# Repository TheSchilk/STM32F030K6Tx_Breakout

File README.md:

# STM32F030K6Tx Breakout

A very simple breakout board for the STM32F030K6Tx MCU. 

Philipp Schilk 2020

https://github.com/TheSchilk/STM32F030K6Tx_Breakout

## Overview

Besides SWD, 2 LEDs, space for a crystal and other supporting circuitry,
there are bells and whistles.

I did however aim to expose as much functionality of the STM as possible:
The crystal is optional and the IO can be exposed with two jumpers if needed.
Also the VDDA Supply can be separated from VDD if a separate supply is wanted.

In fact, with the right jumper configuration this board can serve as a direct
LQFP32 breakout board with all pins exposed and not set connections.

Because I hate nothing more than digging through PDFs to find out what
pins the LEDs where connected to again, I included as much information
as possible in the silkscreen. 

## Features on Board:

**ARM SWD**:  
Connector footprint can accept both an SMD and a TH programming header. 

See [TheSchilk/KiCad_Devices](https://github.com/TheSchilk/KiCad_Devices) for footprint.

**2 LEDs**:
Connected to pins PB0 and PB1

## Compatibility 

According to CubeMX this breakout should also be compatible with:
 - STM32F031K6Tx
 - STM32F051K4Tx
 - STM32F051K6Tx
 - STM32F051K8Tx
 - STM32F042K4Tx
 - STM32F042K6Tx

But that is untested. Please double check the pinout. 

## Jumper Configuration

Here is what the Jumpers do:

JP1: Connects BOOT0 to either GND (indicated by a small arrow) or VDD, both through R1.
JP2: Connects pin F0 of the STM to the breakout header. Should only be set when not
     using a crystal.
JP3: Connects pin F1 of the STM to the breakout header. Should only be set when not
     using a crystal.
JP4: Connects pin 1 of MCU (VDD) to shared VDD  
JP5: Connects pin 16 of MCU (GND) to shared GND  
JP6: Connects pin 17 of MCU (VDD) to shared VDD  
JP7: Connects pin 32 of MCU (GND) to shared GND   
JP8: Connects pin 5 of MCU (VDD) to shared VDD  

Which means, to use this as a STM breakout:  
Set the following jumpers: JP4  JP5  JP6  JP7  JP8  

If you want a straight LQFP Breakout:
Set the following jumpers: JP2 JP3.

## Pinouts

With an STM32F030K6Tx the pinout is as follows:

| *Pin* | *Function* | *Pin* | *Function* |
|-|-|-|-|
| 1 | Vdd  | 32 |  GND |
| 2 | F0 (1) | 31 | BOOT0 |
| 3 | F1 (1) | 30 | PB7 |
| 4 | nRST  | 29 | PB6 |
| 5 | VDDA  | 28 | PB5 |
| 6 | PA0  | 27 | PB4 |
| 7 | PA1  | 26 | PB3 |
| 8 | PA2  | 25 | PA15 |
| 9 | PA3  | 24 | PA14 |
| 10 | PA4 | 23 | PA13 (3) |
| 11 | PA5 | 22 | PA12 (3) |
| 12 | PA6 | 21 | PA11 |
| 13 | PA7 | 20 | PA10 |
| 14 | PB0 (2) | 19 | PA9 |
| 15 | PB1 (2) | 18 | PA8 |
| 16 | GND | 17 | GND |

(1): Crystal
(2): LEDs
(3); SWD

## Releases 
See [Github releases](https://github.com/TheSchilk/STM32F030K6Tx_Breakout/releases) for:  
    - Gerbers  
    - Schematic  
    - Interactive HTML BOM

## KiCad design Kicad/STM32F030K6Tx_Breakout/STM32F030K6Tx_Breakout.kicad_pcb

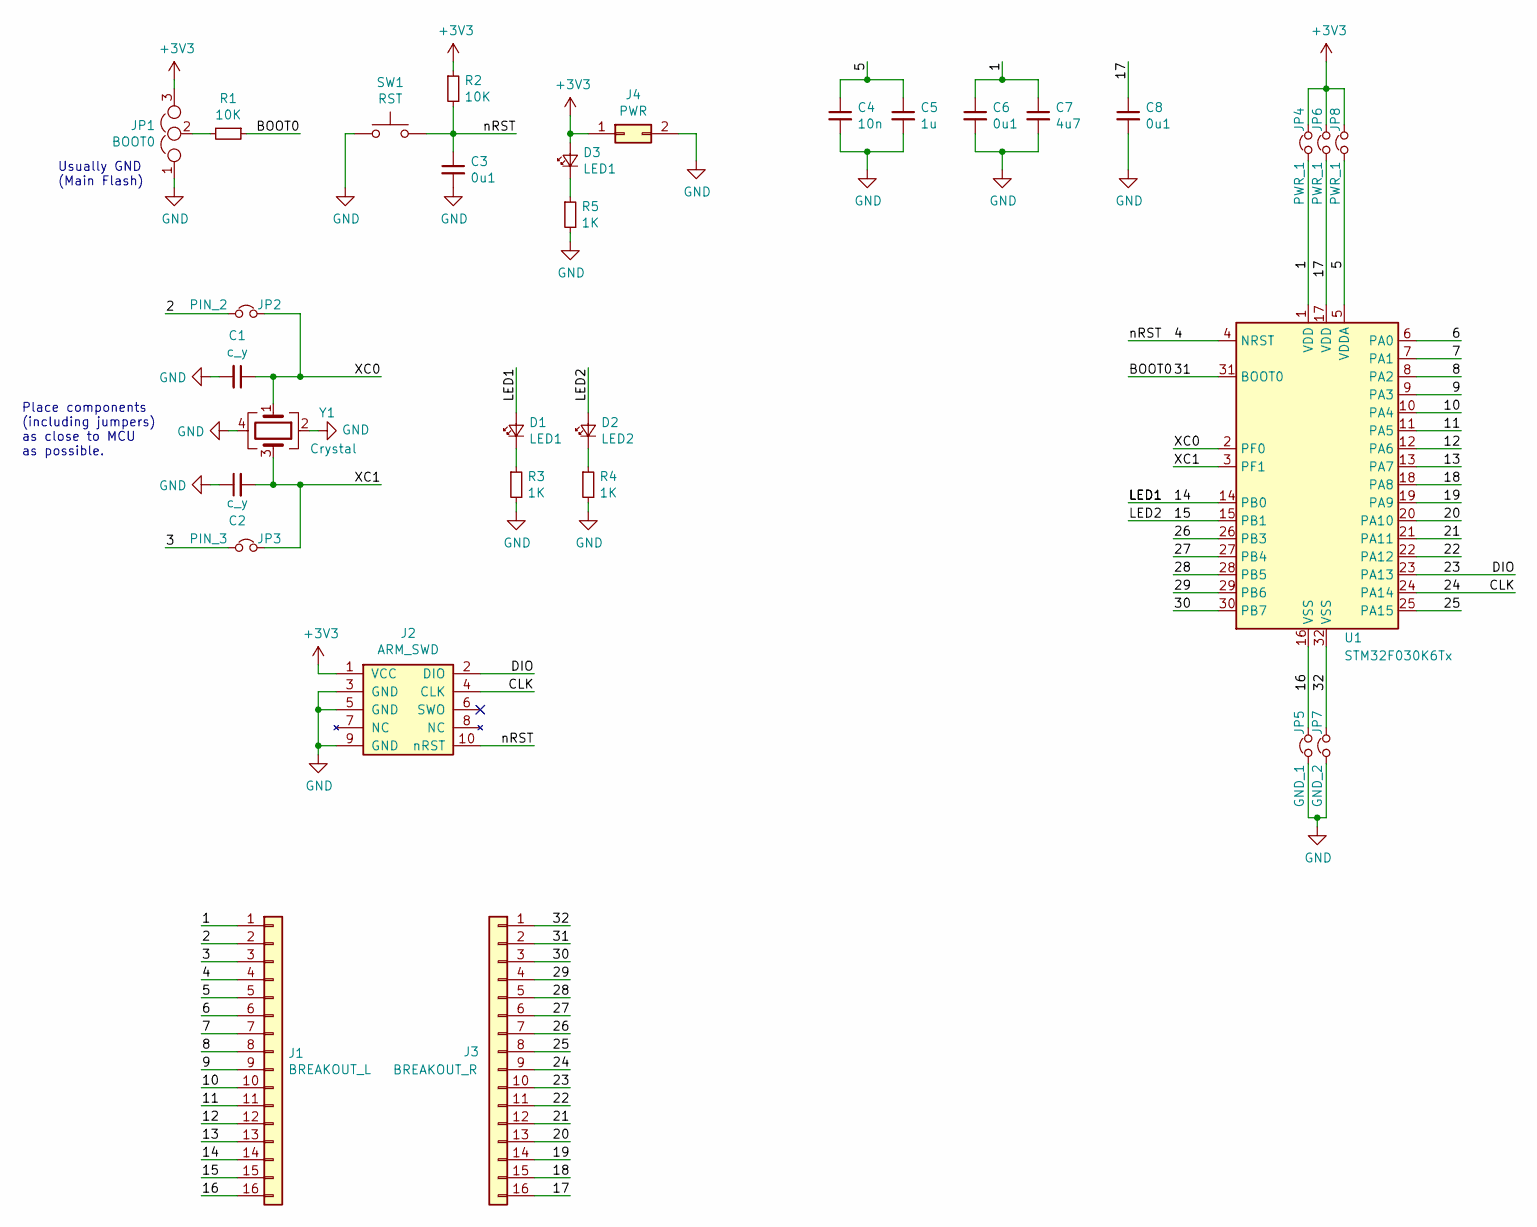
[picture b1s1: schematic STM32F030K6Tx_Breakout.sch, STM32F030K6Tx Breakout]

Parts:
C1, C2: c_y; C_0603_1608Metric
C3, C6, C8: 0u1; C_0603_1608Metric
C4: 10n; C_0603_1608Metric
C5: 1u; C_0603_1608Metric
C7: 4u7; C_0603_1608Metric
D1, D3: LED1; D_0805_2012Metric
D2: LED2; D_0805_2012Metric
J1: BREAKOUT_L; PinHeader_1x16_P2.54mm_Vertical
J2: ARM_SWD; ARM_SWD_SMD_TH
J3: BREAKOUT_R; PinHeader_1x16_P2.54mm_Vertical
J4: PWR; PinHeader_1x02_P2.54mm_Vertical
JP1: BOOT0; SolderJumper-3_P1.3mm_Open_RoundedPad1.0x1.5mm
JP2: PIN_2; SolderJumper-2_P1.3mm_Open_RoundedPad1.0x1.5mm
JP3: PIN_3; SolderJumper-2_P1.3mm_Open_RoundedPad1.0x1.5mm
JP4, JP6, JP8: PWR_1; SolderJumper-2_P1.3mm_Open_RoundedPad1.0x1.5mm
JP5: GND_1; SolderJumper-2_P1.3mm_Open_RoundedPad1.0x1.5mm
JP7: GND_2; SolderJumper-2_P1.3mm_Open_RoundedPad1.0x1.5mm
R1, R2: 10K; R_0603_1608Metric
R3, R4, R5: 1K; R_0603_1608Metric
SW1: RST; SW_PUSH_6mm
U1: STM32F030K6Tx; LQFP-32_7x7mm_P0.8mm
Y1: Crystal; Crystal_SMD_EuroQuartz_MJ-4Pin_5.0x3.2mm

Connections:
+3V3: D3.2 (A), J2.1 (VCC), J4.1, JP1.3, JP4.2, JP6.2, JP8.2, R2.1
/1: C6.1, C7.1, J1.1, JP4.1, U1.1 (VDD)
/2: J1.2, JP2.1
/3: J1.3, JP3.1
/4: C3.1, J1.4, J2.10 (nRST), R2.2, SW1.2, U1.4 (NRST)
/5: C4.1, C5.1, J1.5, JP8.1, U1.5 (VDDA)
/6: J1.6, U1.6 (PA0)
/7: J1.7, U1.7 (PA1)
/8: J1.8, U1.8 (PA2)
/9: J1.9, U1.9 (PA3)
/10: J1.10, U1.10 (PA4)
/11: J1.11, U1.11 (PA5)
/12: J1.12, U1.12 (PA6)
/13: J1.13, U1.13 (PA7)
/14: D1.2 (A), J1.14, U1.14 (PB0)
/15: D2.2 (A), J1.15, U1.15 (PB1)
/16: J1.16, JP5.2, U1.16 (VSS)
/17: C8.1, J3.16, JP6.1, U1.17 (VDD)
/18: J3.15, U1.18 (PA8)
/19: J3.14, U1.19 (PA9)
/20: J3.13, U1.20 (PA10)
/21: J3.12, U1.21 (PA11)
/22: J3.11, U1.22 (PA12)
/23: J2.2 (DIO), J3.10, U1.23 (PA13)
/24: J2.4 (CLK), J3.9, U1.24 (PA14)
/25: J3.8, U1.25 (PA15)
/26: J3.7, U1.26 (PB3)
/27: J3.6, U1.27 (PB4)
/28: J3.5, U1.28 (PB5)
/29: J3.4, U1.29 (PB6)
/30: J3.3, U1.30 (PB7)
/31: J3.2, R1.1, U1.31 (BOOT0)
/32: J3.1, JP7.2, U1.32 (VSS)
/XC0: C1.1, JP2.2, U1.2 (PF0), Y1.1
/XC1: C2.2, JP3.2, U1.3 (PF1), Y1.3
GND: C1.2, C2.1, C3.2, C4.2, C5.2, C6.2, C7.2, C8.2, J2.3 (GND), J2.5 (GND), J2.9 (GND), J4.2, JP1.1, JP5.1, JP7.1, R3.2, R4.2, R5.2, SW1.1, Y1.2, Y1.4
unnamed: D1.1 (K), R3.1
unnamed: D2.1 (K), R4.1
unnamed: D3.1 (K), R5.1
unnamed: JP1.2, R1.2

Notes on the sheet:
Usually GND (Main Flash)
Place components (including jumpers) as close to MCU as possible.

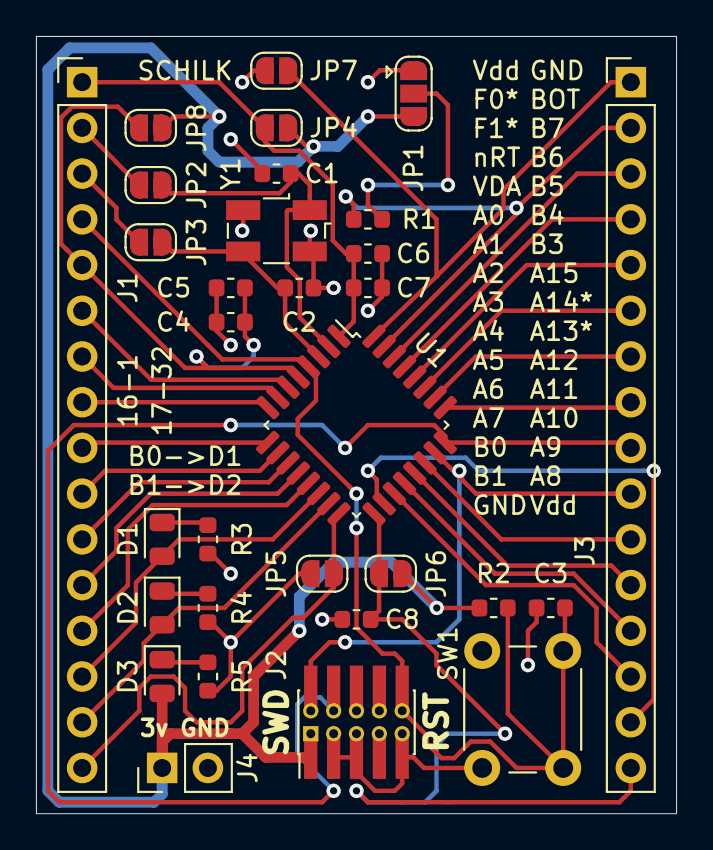
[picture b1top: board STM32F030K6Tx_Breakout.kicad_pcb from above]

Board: 2 copper layers, 35.6 x 43.2 mm, 31 parts (0 on the bottom side), 40 nets.

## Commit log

2020-06-06 Added v0.1
2020-06-06 Small README Update
2020-06-06 Added missing picture...
2020-06-15 Small fixes to the README
2020-06-21 Fixed small mistake in documentation
2020-09-22 Added Interactive BOM, reorderd Files.
2021-05-24 Added .gitattributes
